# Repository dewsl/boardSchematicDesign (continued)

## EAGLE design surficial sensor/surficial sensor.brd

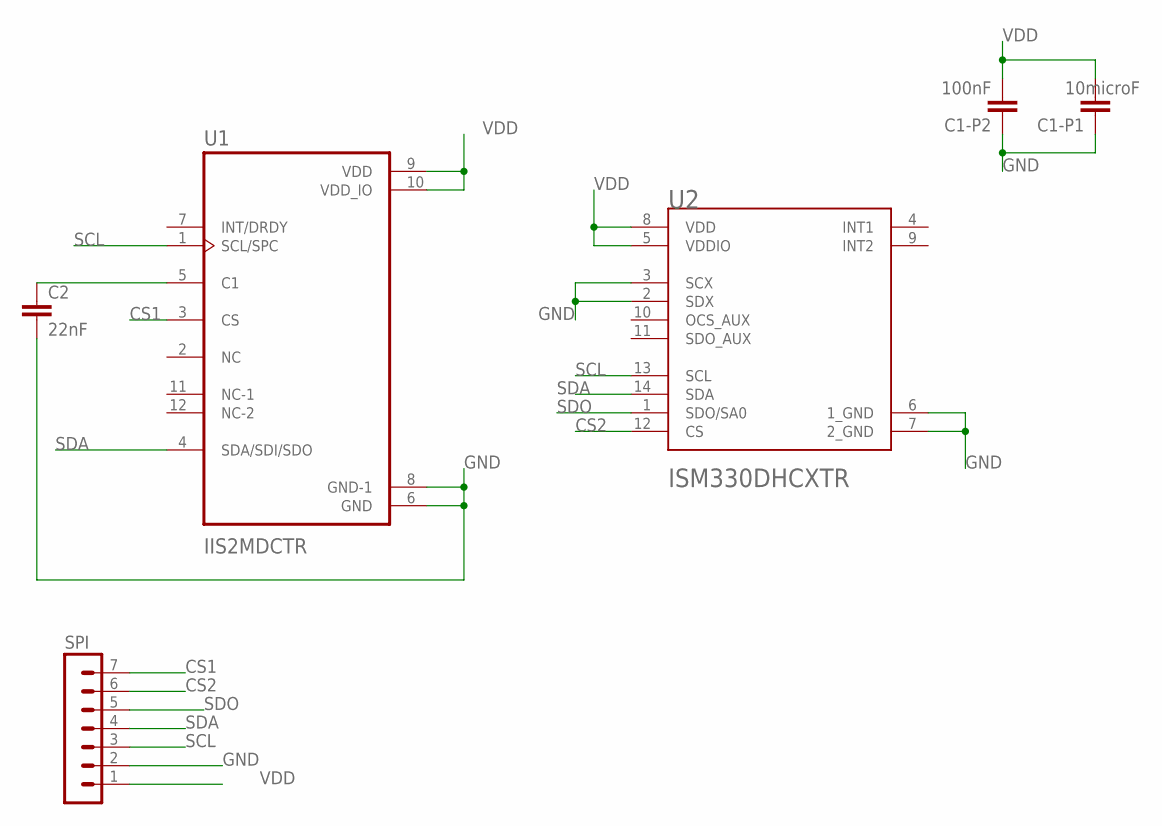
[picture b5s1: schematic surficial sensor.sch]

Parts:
C1-P1: 10microF; C0603
C1-P2: 100nF; C0603
C2: 22nF; C0603
SPI: MA07-1
U1: IIS2MDCTR; LGA12R50P4X4_200X200X70
U2: STMICROELECTRONICS_ISM330DHCXTRSTMICROELECTRONICS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; STMICROELECTRONICS_ISM330DHCXTR_0

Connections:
CS1: SPI.7, U1.3 (CS)
CS2: SPI.6, U2.12 (CS)
GND: C1-P1.1, C1-P2.1, C2.2, SPI.2, U1.6 (GND), U1.8 (GND-1), U2.2 (SDX), U2.3 (SCX), U2.6 (1_GND), U2.7 (2_GND)
unnamed: C2.1, U1.5 (C1)
SCL: SPI.3, U1.1 (SCL/SPC), U2.13 (SCL)
SDA: SPI.4, U1.4 (SDA/SDI/SDO), U2.14 (SDA)
SDO: SPI.5, U2.1 (SDO/SA0)
VDD: C1-P1.2, C1-P2.2, SPI.1, U1.9 (VDD), U1.10 (VDD_IO), U2.5 (VDDIO), U2.8 (VDD)

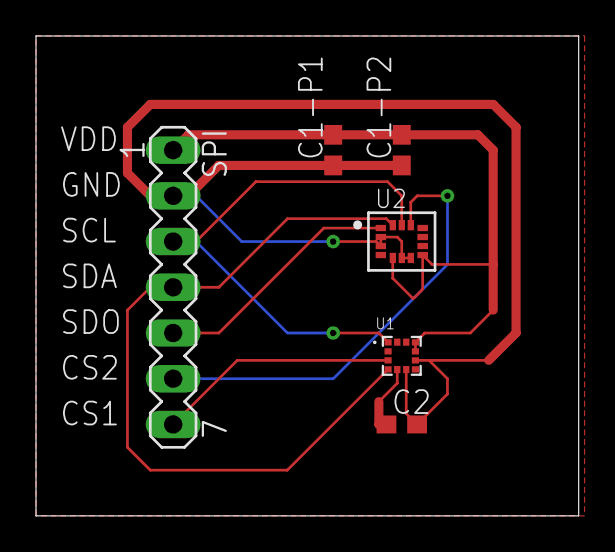
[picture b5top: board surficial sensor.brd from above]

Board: 2 copper layers, 30.1 x 26.7 mm, 6 parts (0 on the bottom side), 8 nets.

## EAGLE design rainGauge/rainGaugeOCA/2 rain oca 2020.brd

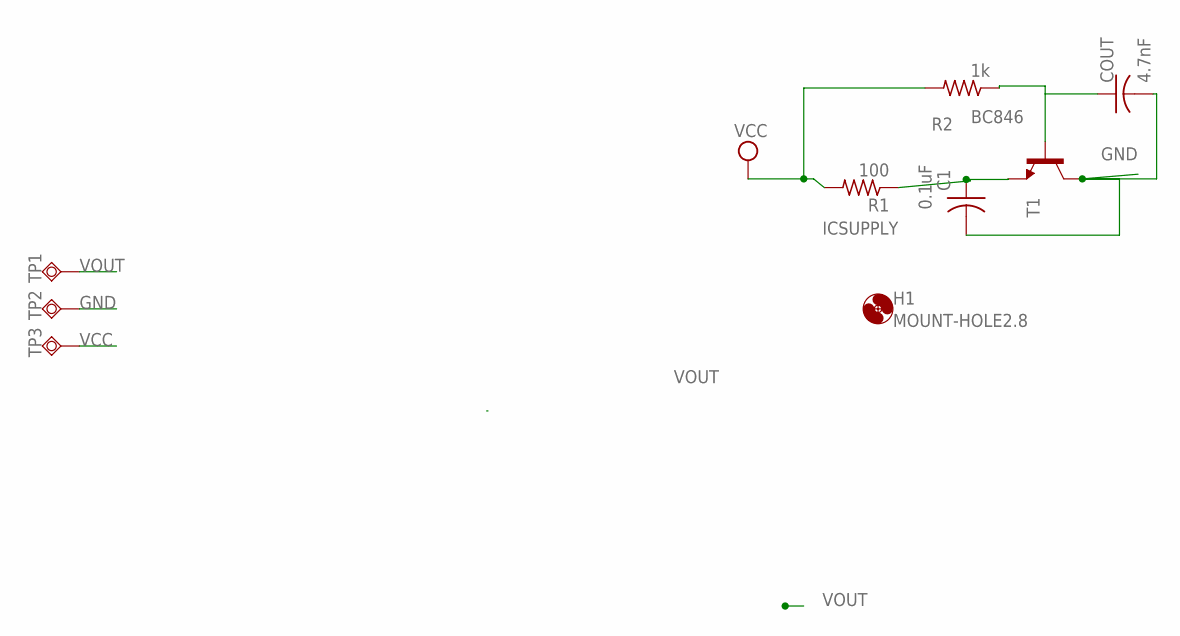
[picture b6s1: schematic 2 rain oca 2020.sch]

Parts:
C1: 0.1uF; C0402
COUT: 4.7nF; C0402
H1: MOUNT-HOLE2.8; 2,8
R1: 100; R0603
R2: 1k; R0603
T1: BC846; SOT23
TP1, TP2, TP3: TPSQTP20SQ; TP20SQ

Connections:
GND: C1.2, COUT.2, T1.3 (C), TP2.TP
ICSUPPLY: C1.1, R1.1, T1.2 (E)
VCC: R1.2, R2.2, TP3.TP
VOUT: COUT.1, R2.1, T1.1 (B), TP1.TP

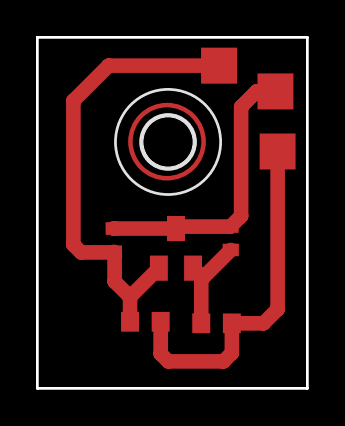
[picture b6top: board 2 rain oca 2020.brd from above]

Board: 2 copper layers, 15.0 x 19.5 mm, 9 parts (0 on the bottom side), 4 nets.

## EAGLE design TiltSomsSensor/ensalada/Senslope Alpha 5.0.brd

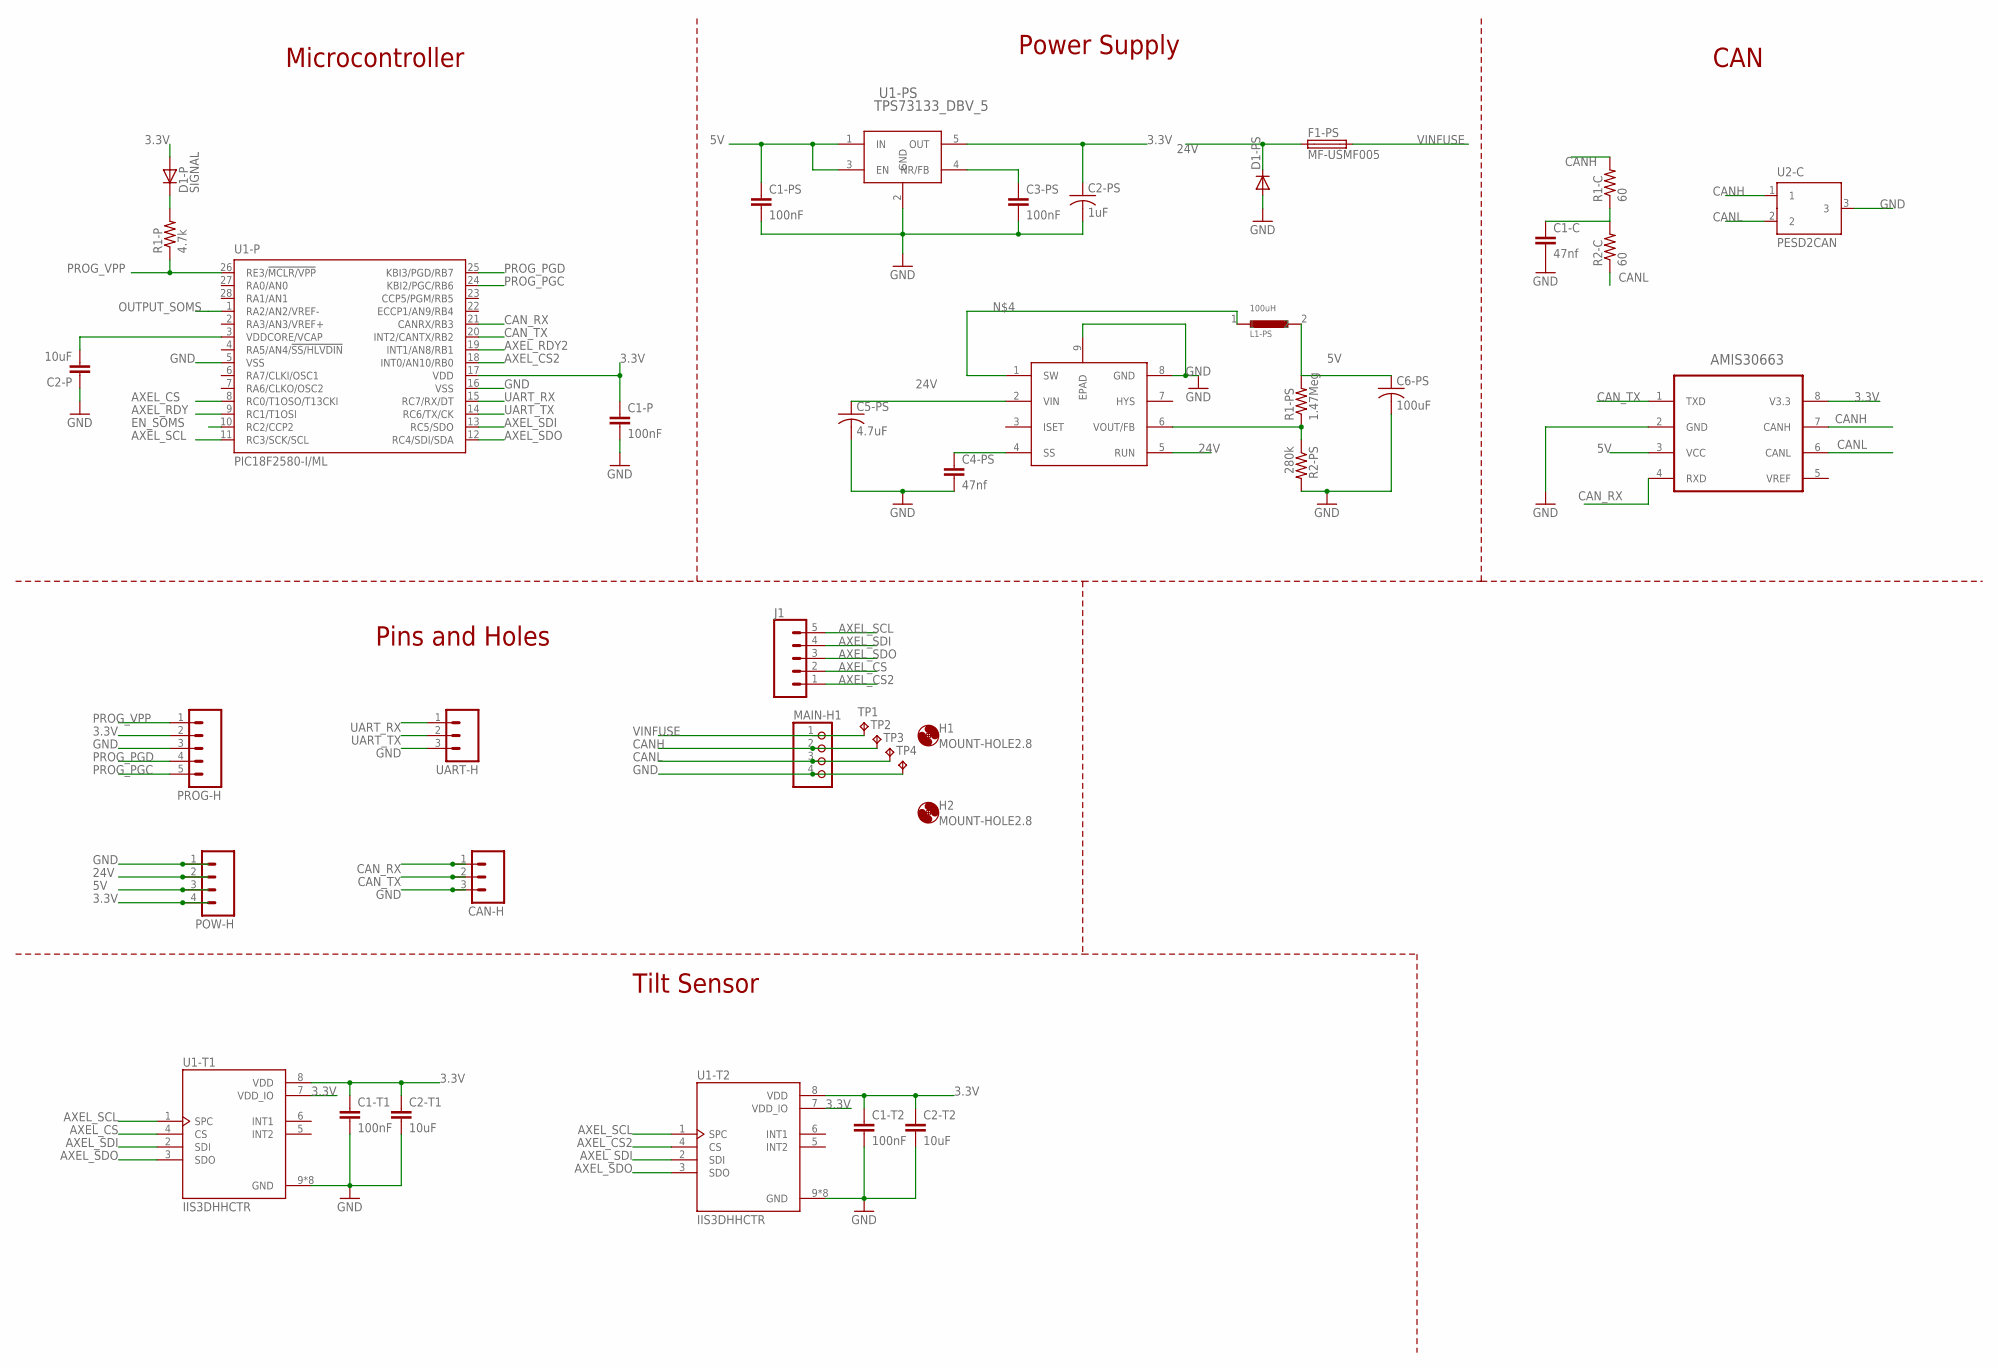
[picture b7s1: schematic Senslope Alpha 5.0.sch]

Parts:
C1-C, C4-PS: 47nf; C0805
C1-P, C1-PS, C1-T1, C1-T2, C3-PS: 100nF; C0603
C2-P, C2-T1, C2-T2: 10uF; C0603
C2-PS: 1uF; C0402
C5-PS: 4.7uF; C1206K
C6-PS: 100uF; C1210K
CAN-H: UART; 1X03_NO_SILK
D1-P: SIGNAL; DIODE-0603
D1-PS: DIODE-DO-214AC; DO-214AC
F1-PS: MF-USMF005; 1210
H1, H2: MOUNT-HOLE2.8; 2,8
J1: CONN_05NO_SILK; 1X05_NO_SILK
L1-PS: 100uH; 1210
MAIN-H1: PINHD-1X04_2.54; 1X04
POW-H: M041X04_NO_SILK; 1X04_NO_SILK
PROG-H: M05PTH; 1X05@1
R1-C, R2-C: 60; R0805
R1-P: 4.7k; R0603
R1-PS: 1.47Meg; R0805
R2-PS: 280k; R0805
TP1, TP2, TP3, TP4: TPTP10SQ; TP10SQ
U1-P: PIC18F2580-I/ML; QFN28-ML_6X6MM
U1-PS: TPS73133_DBV_5; DBV5
U1-T1, U1-T2: IIS3DHHCTR; IC_IIS3DHHCTR
U2: AMIS30663CAN; SOIC8
U2-C: PESD2CAN; SOT23
U2-PS: LTC3631-5; MSOP8E
UART-H: UART; 1X03_NO_SILK

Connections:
3.3V: C1-P.1, C1-T1.1, C1-T2.1, C2-PS.1, C2-T1.1, C2-T2.1, D1-P.A, POW-H.4, PROG-H.2, U1-P.17 (VDD), U1-PS.5 (OUT), U1-T1.7 (VDD_IO), U1-T1.8 (VDD), U1-T2.7 (VDD_IO), U1-T2.8 (VDD), U2.8 (V3.3)
5V: C1-PS.1, C6-PS.1, L1-PS.2, POW-H.3, R1-PS.2, U1-PS.1 (IN), U1-PS.3 (EN), U2.3 (VCC)
24V: C5-PS.1, D1-PS.1 (C), F1-PS.1, POW-H.2, U2-PS.2 (VIN), U2-PS.5 (RUN)
AXEL_CS: J1.2, U1-P.8 (RC0/T1OSO/T13CKI), U1-T1.4 (CS)
AXEL_CS2: J1.1, U1-P.18 (INT0/AN10/RB0), U1-T2.4 (CS)
AXEL_RDY: U1-P.9 (RC1/T1OSI)
AXEL_RDY2: U1-P.19 (INT1/AN8/RB1)
AXEL_SCL: J1.5, U1-P.11 (RC3/SCK/SCL), U1-T1.1 (SPC), U1-T2.1 (SPC)
AXEL_SDI: J1.4, U1-P.13 (RC5/SDO), U1-T1.2 (SDI), U1-T2.2 (SDI)
AXEL_SDO: J1.3, U1-P.12 (RC4/SDI/SDA), U1-T1.3 (SDO), U1-T2.3 (SDO)
CANH: MAIN-H1.2, R1-C.2, TP2.TP, U2.7 (CANH), U2-C.1
CANL: MAIN-H1.3, R2-C.1, TP3.TP, U2.6 (CANL), U2-C.2
CAN_RX: CAN-H.1, U1-P.21 (CANRX/RB3), U2.4 (RXD)
CAN_TX: CAN-H.2, U1-P.20 (INT2/CANTX/RB2), U2.1 (TXD)
EN_SOMS: U1-P.10 (RC2/CCP2)
GND: C1-C.2, C1-P.2, C1-PS.2, C1-T1.2, C1-T2.2, C2-P.1, C2-PS.2, C2-T1.2, C2-T2.2, C3-PS.2, C4-PS.2, C5-PS.2, C6-PS.2, CAN-H.3, D1-PS.2 (A), MAIN-H1.4, POW-H.1, PROG-H.3, R2-PS.2, TP4.TP, U1-P.5 (VSS), U1-P.16 (VSS), U1-PS.2 (GND), U1-T1.9 (GND), U1-T1.10 (GND), U1-T1.11 (GND), U1-T1.12 (GND), U1-T1.13 (GND), U1-T1.14 (GND), U1-T1.15 (GND), U1-T1.16 (GND), U1-T2.9 (GND), U1-T2.10 (GND), U1-T2.11 (GND), U1-T2.12 (GND), U1-T2.13 (GND), U1-T2.14 (GND), U1-T2.15 (GND), U1-T2.16 (GND), U2.2 (GND), U2-C.3, U2-PS.8 (GND), U2-PS.9 (EPAD), UART-H.3
unnamed: C1-C.1, R1-C.1, R2-C.2
unnamed: L1-PS.1, U2-PS.1 (SW)
unnamed: C3-PS.1, U1-PS.4 (NR/FB)
unnamed: R1-PS.1, R2-PS.1, U2-PS.6 (VOUT/FB)
unnamed: D1-P.C, R1-P.2
unnamed: C4-PS.1, U2-PS.4 (SS)
unnamed: C2-P.2, U1-P.3 (VDDCORE/VCAP)
OUTPUT_SOMS: U1-P.1 (RA2/AN2/VREF-)
PROG_PGC: PROG-H.5, U1-P.24 (KBI2/PGC/RB6)
PROG_PGD: PROG-H.4, U1-P.25 (KBI3/PGD/RB7)
PROG_VPP: PROG-H.1, R1-P.1, U1-P.26 (RE3/!MCLR/VPP)
UART_RX: U1-P.15 (RC7/RX/DT), UART-H.1
UART_TX: U1-P.14 (RC6/TX/CK), UART-H.2
VINFUSE: F1-PS.2, MAIN-H1.1, TP1.TP

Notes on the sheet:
Microcontroller
Power Supply
CAN
Pins and Holes
Tilt Sensor

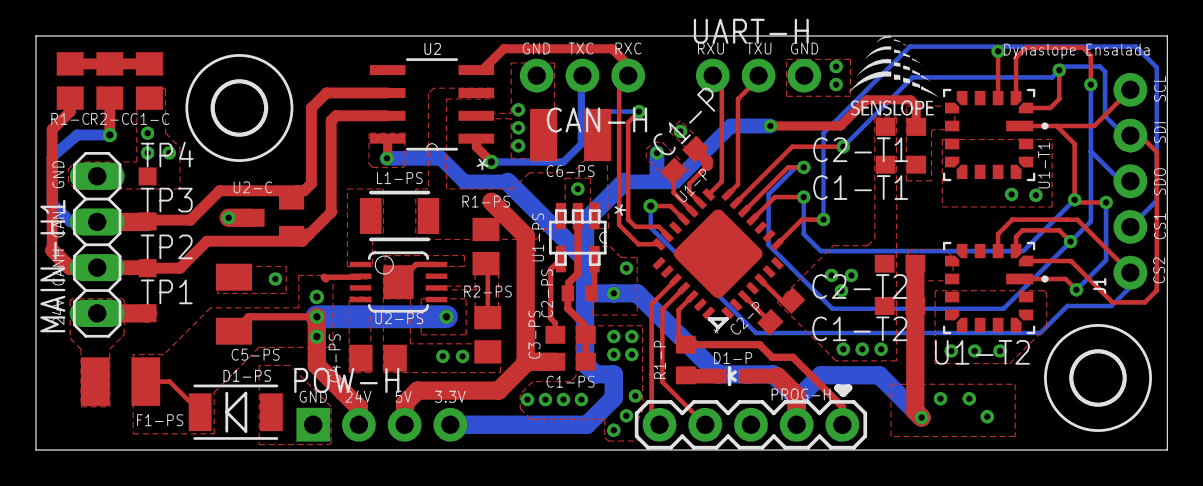
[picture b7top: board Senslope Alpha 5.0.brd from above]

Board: 2 copper layers, 62.9 x 23.0 mm, 42 parts (0 on the bottom side), 26 nets.

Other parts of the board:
U$1: LOGO_SML_TNAME

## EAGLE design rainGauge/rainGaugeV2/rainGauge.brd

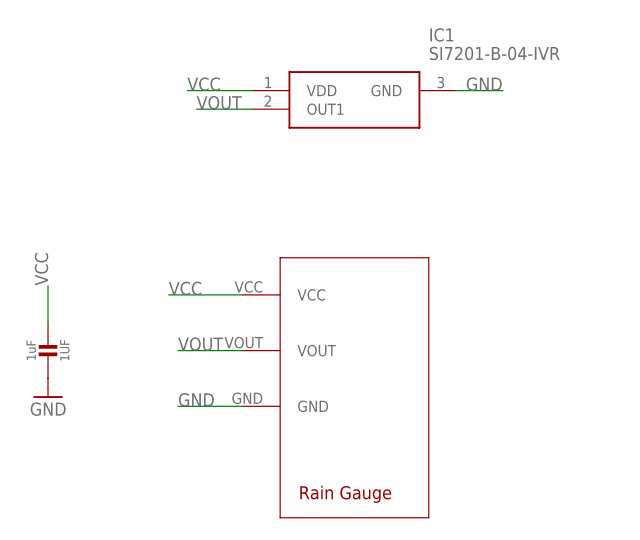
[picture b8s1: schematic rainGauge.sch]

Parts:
1UF: 1uF; 0805-NO
IC1: SI7201-B-04-IVR; SOT95P275X125-3N
U$1: RAINGAUGERAINPAD; RAINGAUGE

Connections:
GND: 1UF.1, IC1.3 (GND), U$1.GND
VCC: 1UF.2, IC1.1 (VDD), U$1.VCC
VOUT: IC1.2 (OUT1), U$1.VOUT

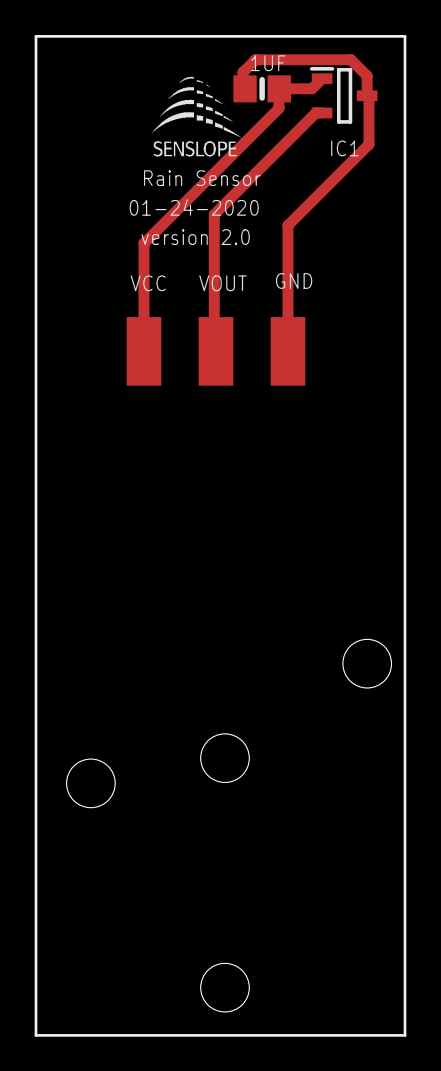
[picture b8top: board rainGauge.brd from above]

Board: 2 copper layers, 20.5 x 55.5 mm, 4 parts (0 on the bottom side), 3 nets.

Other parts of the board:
U$2: LOGO_SML_TNAME

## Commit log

2018-06-07 Initial commit for customDue_habhab
2018-06-07 Initial commit of tilt_dinuguan sensor
2018-06-07 Added Extensometer Transmitter schematic and board file
2018-06-07 Added extensometer receiver schematic and board files
2018-06-28 Lidar proto-board
2018-07-06 updated route, rtc alarm update
2018-09-25 corrected the sd card slot
2018-09-25 added scr file
2018-09-25 added b_13
2019-02-08 added rpi gsm shield version 2
2019-04-05 rpi-gsm-lora shield
2019-05-16 updated schematic and layout for switching function added CAMOutputs
2019-05-16 added ptc fuse from 5V out to rpi
2019-05-19 added gerber files of the board
2019-05-19 finalize gerber files repair outline of board
2019-07-12 updated due LoRa shield interface rtc enabled low power m0 module
2019-07-15 finalized board details
2020-01-24 - si7201 rain gauge sensor
2020-01-27 +oscar raingauge
2020-08-13 +added surficial sensor
2022-05-19 **MAD updated files
2022-05-19 -added pcb files of custom due alternative
